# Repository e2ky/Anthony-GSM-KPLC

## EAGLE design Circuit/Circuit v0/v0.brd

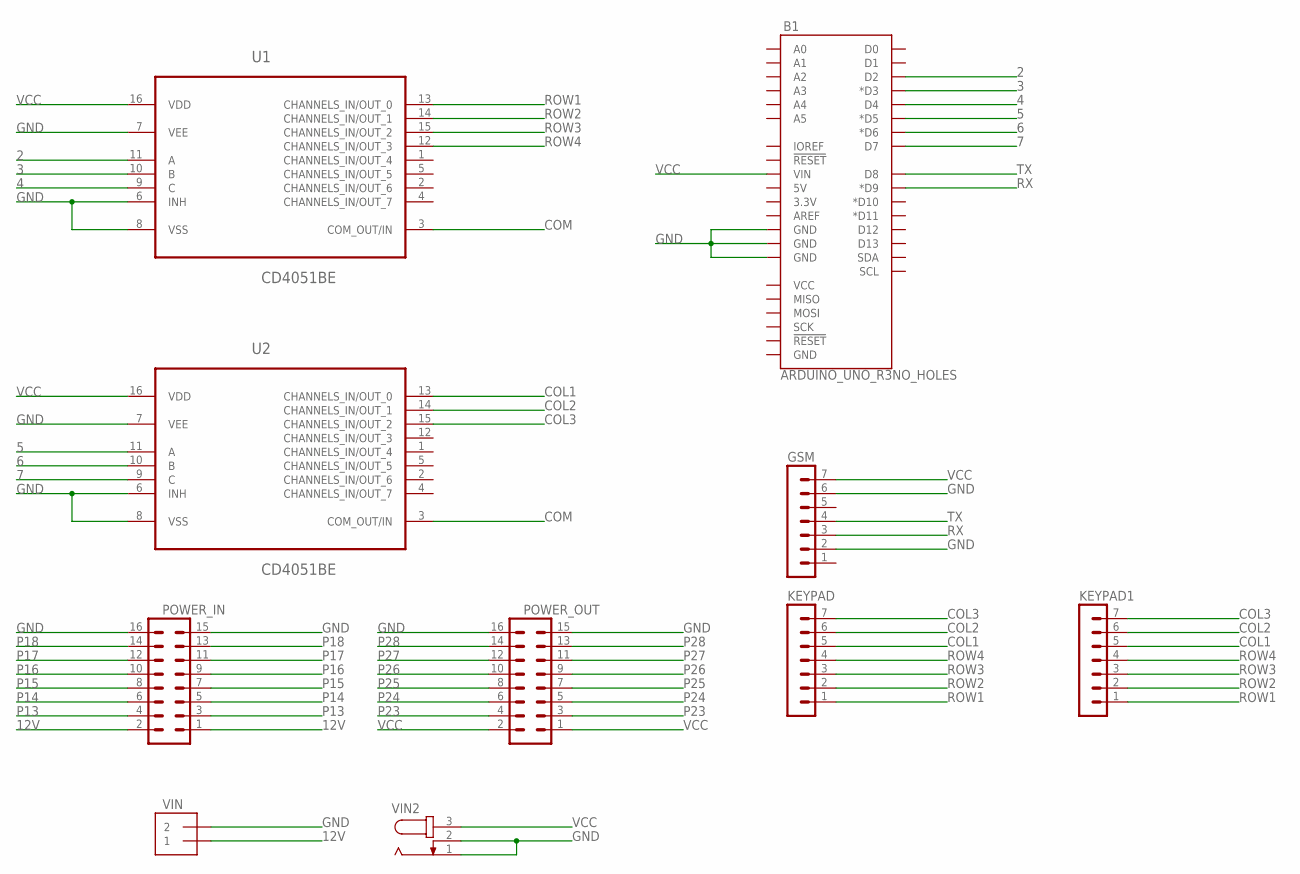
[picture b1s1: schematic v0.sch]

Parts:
B1: ARDUINO_UNO_R3NO_HOLES; ARDUINO_R3_NO_HOLES
GSM: MA07-1
KEYPAD, KEYPAD1: MA07-1
POWER_IN: MA08-2
POWER_OUT: MA08-2
U1, U2: CD4051BE; DIP254P762X508-16
VIN: 1X2-3.5MM
VIN2: JACK-PLUG0; SPC4077

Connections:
2: B1.D2, U1.11 (A)
3: B1.D3 (*D3), U1.10 (B)
4: B1.D4, U1.9 (C)
5: B1.D5 (*D5), U2.11 (A)
6: B1.D6 (*D6), U2.10 (B)
7: B1.D7, U2.9 (C)
12V: POWER_IN.1, POWER_IN.2, VIN.1
COL1: KEYPAD.5, KEYPAD1.5, U2.13 (CHANNELS_IN/OUT_0)
COL2: KEYPAD.6, KEYPAD1.6, U2.14 (CHANNELS_IN/OUT_1)
COL3: KEYPAD.7, KEYPAD1.7, U2.15 (CHANNELS_IN/OUT_2)
COM: U1.3 (COM_OUT/IN), U2.3 (COM_OUT/IN)
GND: B1.GND@2 (GND), B1.GND@3 (GND), B1.GND@4 (GND), GSM.2, GSM.6, POWER_IN.15, POWER_IN.16, POWER_OUT.15, POWER_OUT.16, U1.6 (INH), U1.7 (VEE), U1.8 (VSS), U2.6 (INH), U2.7 (VEE), U2.8 (VSS), VIN.2, VIN2.1, VIN2.2
P13: POWER_IN.3, POWER_IN.4
P14: POWER_IN.5, POWER_IN.6
P15: POWER_IN.7, POWER_IN.8
P16: POWER_IN.9, POWER_IN.10
P17: POWER_IN.11, POWER_IN.12
P18: POWER_IN.13, POWER_IN.14
P23: POWER_OUT.3, POWER_OUT.4
P24: POWER_OUT.5, POWER_OUT.6
P25: POWER_OUT.7, POWER_OUT.8
P26: POWER_OUT.9, POWER_OUT.10
P27: POWER_OUT.11, POWER_OUT.12
P28: POWER_OUT.13, POWER_OUT.14
ROW1: KEYPAD.1, KEYPAD1.1, U1.13 (CHANNELS_IN/OUT_0)
ROW2: KEYPAD.2, KEYPAD1.2, U1.14 (CHANNELS_IN/OUT_1)
ROW3: KEYPAD.3, KEYPAD1.3, U1.15 (CHANNELS_IN/OUT_2)
ROW4: KEYPAD.4, KEYPAD1.4, U1.12 (CHANNELS_IN/OUT_3)
RX: B1.D9 (*D9), GSM.3
TX: B1.D8, GSM.4
VCC: B1.VIN, GSM.7, POWER_OUT.1, POWER_OUT.2, U1.16 (VDD), U2.16 (VDD), VIN2.3

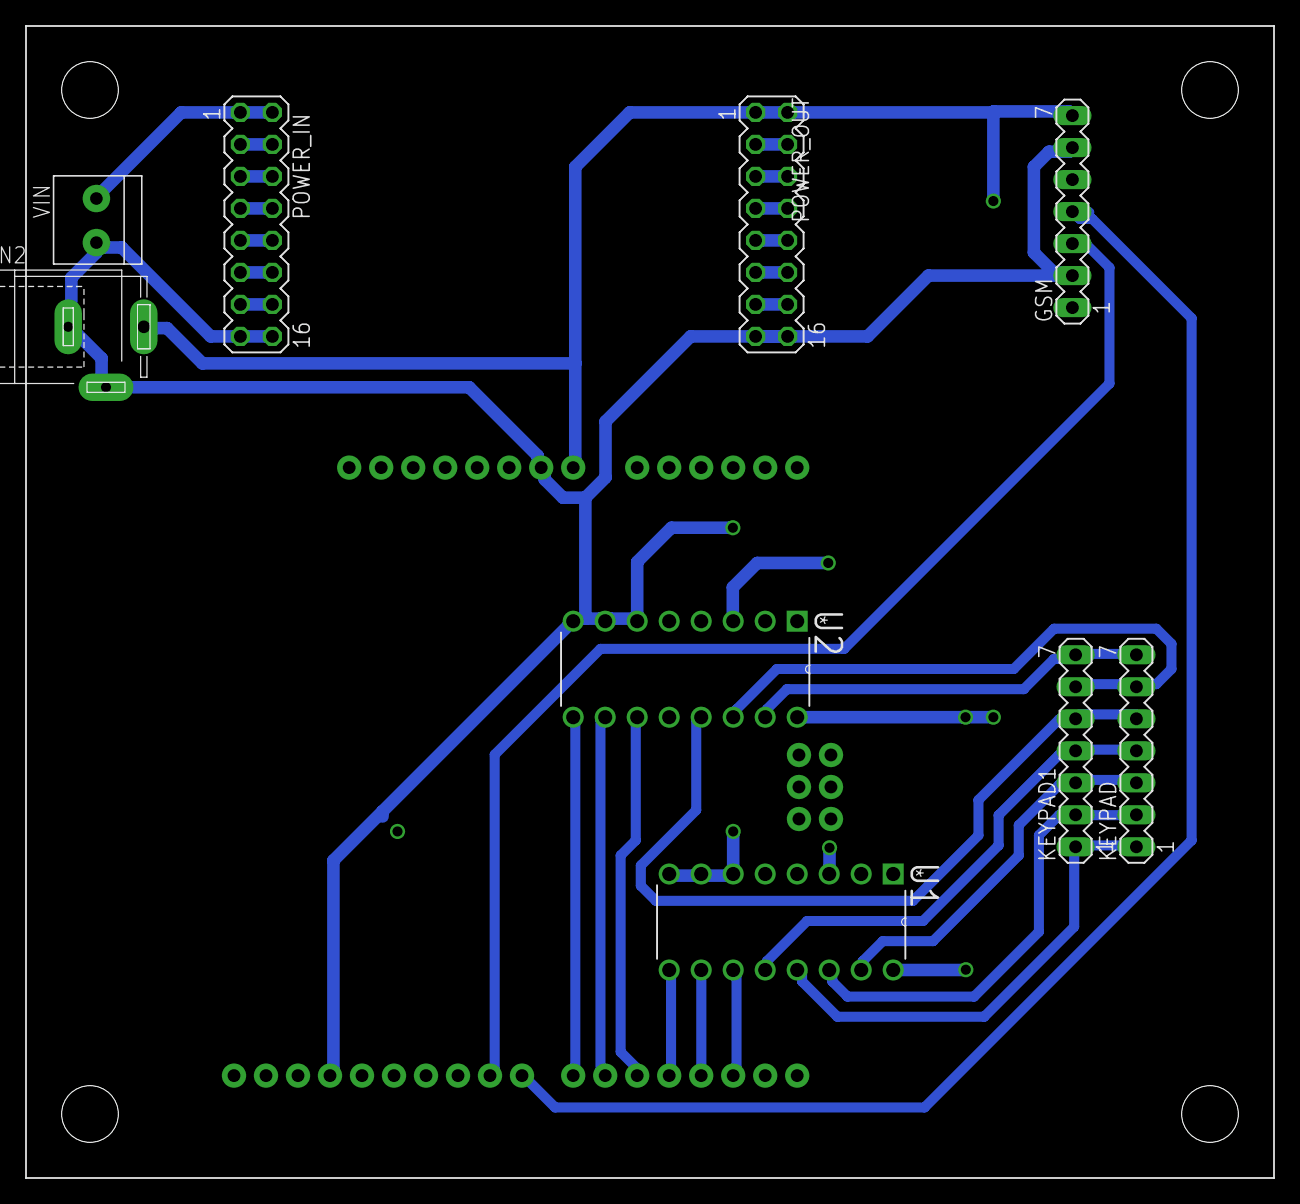
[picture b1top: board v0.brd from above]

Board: 2 copper layers, 99.1 x 91.4 mm, 10 parts (1 on the bottom side), 31 nets.

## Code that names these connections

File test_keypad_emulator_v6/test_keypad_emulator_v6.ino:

/*
    Arduino Uno Keypad Emulation
    By:- Kim
    Date: 19-06-2021
*/

char inChar;     // setup  for data storage

boolean newData = false;

int col1 = 4;
int col2 = 5;
int col3 = 6;
int row1 = 7;
int row2 = 8;
int row3 = 9;
int row4 = 10;

void setup() 
{
  Serial.begin(9600);

  Serial.println("Initializing...");
  delay(1000);

  //set all pins as outputs
  pinMode (col1, OUTPUT);
  pinMode (col2, OUTPUT);
  pinMode (col3, OUTPUT);
  pinMode (row1, OUTPUT);
  pinMode (row2, OUTPUT);
  pinMode (row3, OUTPUT);
  pinMode (row4, OUTPUT);

}

void loop()
{
  recvData();
}

void recvData()
{
  while (Serial.available())
  {
    inChar = (char)Serial.read();     // get new byte
    emulate();
  }
}

void emulate()
{
  Serial.print("Emulating...");
  Serial.write(inChar);
  switch (inChar)
  {
    case 1:
      digitalWrite (col1, HIGH);
      digitalWrite (col2, LOW);
      digitalWrite (col3, LOW);
      digitalWrite (row1, HIGH);
      digitalWrite (row2, LOW);
      digitalWrite (row3, LOW);
      digitalWrite (row4, LOW);
      break;

    case 2:
      digitalWrite (col1, LOW);
      digitalWrite (col2, HIGH);
      digitalWrite (col3, LOW);
      digitalWrite (row1, HIGH);
      digitalWrite (row2, LOW);
      digitalWrite (row3, LOW);
      digitalWrite (row4, LOW);
      break;

    case 3:
      digitalWrite (col1, LOW);
      digitalWrite (col2, LOW);
      digitalWrite (col3, HIGH);
      digitalWrite (row1, HIGH);
      digitalWrite (row2, LOW);
      digitalWrite (row3, LOW);
      digitalWrite (row4, LOW);
      break;

    case 4:
      digitalWrite (col1, HIGH);
      digitalWrite (col2, LOW);
      digitalWrite (col3, LOW);
      digitalWrite (row1, LOW);
      digitalWrite (row2, HIGH);
      digitalWrite (row3, LOW);
      digitalWrite (row4, LOW);
      break;

    case 5:
      digitalWrite (col1, LOW);
      digitalWrite (col2, HIGH);
      digitalWrite (col3, LOW);
      digitalWrite (row1, LOW);
      digitalWrite (row2, HIGH);
      digitalWrite (row2, LOW);
      digitalWrite (row3, LOW);
      digitalWrite (row4, LOW);
      break;

    case 6:
      digitalWrite (col1, LOW);
      digitalWrite (col2, LOW);
      digitalWrite (col3, HIGH);
      digitalWrite (row1, LOW);
      digitalWrite (row2, HIGH);
      digitalWrite (row3, LOW);
      digitalWrite (row4, LOW);
      break;

    case 7:
      digitalWrite (col1, HIGH);
      digitalWrite (col2, LOW);
      digitalWrite (col3, LOW);
      digitalWrite (row1, LOW);
      digitalWrite (row2, LOW);
      digitalWrite (row3, HIGH);
      digitalWrite (row4, LOW);
      break;

    case 8:
      digitalWrite (col1, LOW);
      digitalWrite (col2, HIGH);
      digitalWrite (col3, LOW);
      digitalWrite (row1, LOW);
      digitalWrite (row2, LOW);
      digitalWrite (row3, HIGH);
      digitalWrite (row4, LOW);
      break;

    case 9:
      digitalWrite (col1, LOW);
      digitalWrite (col2, LOW);
      digitalWrite (col3, HIGH);
      digitalWrite (row1, LOW);
      digitalWrite (row2, LOW);
      digitalWrite (row3, HIGH);
      digitalWrite (row4, LOW);
      break;

    case '*':
      digitalWrite (col1, HIGH);
      digitalWrite (col2, LOW);
      digitalWrite (col3, LOW);
      digitalWrite (row1, LOW);
      digitalWrite (row2, LOW);
      digitalWrite (row3, LOW);
      digitalWrite (row4, HIGH);
      break;

    case 0:
      digitalWrite (col1, LOW);
      digitalWrite (col2, HIGH);
      digitalWrite (col3, LOW);
      digitalWrite (row1, LOW);
      digitalWrite (row2, LOW);
      digitalWrite (row3, LOW);
      digitalWrite (row4, HIGH);
      break;

    case '#':
      digitalWrite (col1, LOW);
      digitalWrite (col2, LOW);
      digitalWrite (col3, HIGH);
      digitalWrite (row1, LOW);
      digitalWrite (row2, LOW);
      digitalWrite (row3, LOW);
      digitalWrite (row4, HIGH);
      break;

  }
  delay (10);
}

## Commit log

2020-08-07 initial
2020-11-18 keypad emulation code'
2021-05-05 serial read and parse
2021-09-29 Improved test code
2021-09-29 Better? sms test code
2021-09-29 Keypad emulation test code
2021-09-29 Final code?
2021-09-29 Circuit moved from breadboard, done in Eagle and include png for milling on modela 1/64 for trace milling and 1/32 for drill holes and outline
2021-10-15 v0 smaller and removed KiCAD files
2021-11-13 circuit for fabrication
2021-12-15 final code

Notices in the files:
parts and their libraries:
SparkFun-Boards: Licensing: Creative Commons ShareAlike 4.0 International - https://creativecommons.org/licenses/by-sa/4.0
